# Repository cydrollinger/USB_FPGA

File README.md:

<a href="https://elec-real.com/case-studies/usb-fpga/"></img></a>

> Electronic Realization L.L.C.								  
> Design: Open Hardware Source   USB Configurable Field Programmable Gate Array  	  
>						USB_FPGA board				   
> License: TAPR - http://www.tapr.org/OHL						   
> Engineer: Cy Drollinger								   
> Date: June 26th, 2012								           
> Email: cy@elec-real.com
>Website: https://elec-real.com								   
> Address: 2023 Stadium Dr Suite 2B #210 Bozeman, MT 59715				   
> Phone: 406-539-8117									   

**NOTE:**
 This design has been tested and functions as specified. The design is provided gratis, so, please 
 think critically while utilizing and or redesigning. Open electronic circuitry can be dangerous due 
 to easily shorting circuits which can generate immediate and intense heat resulting in fire. Conversation is
 welcome to improve this design and repository, but, be advised ER is a professional design house and
 monetary compensation is required for additional work toward this design enabling your success.			   

**PURPOSE:**

>**File Arcitecture with a terse description**

* FOLDERS:
	* CDM 2.04.16 WHQL Certified (FTDI.com)
		* WINXP drivers necessary to implement USB configuration of the FPGA (older)
	* CDM 2.04.16 WHQL Certified (FTDI.com)
		* WINXP drivers necessary to implement USB configuration of the FPGA (newer)
	
	* USB_CMD/USB_FPGA: - batch files converting a text document of VHDL into a binary for programming the XC3S250E
		* bin
		* clean
		* clean
		* done_100e.bin
		* done_250e.bin
		* fpga
		* fpga
		* generate
		* generate_100e
		* make
		* make_100e
		* readme
		
	* DOCS/USB_FPGA:
		* may 27 - The goals at the start of the design and the resources utilized 
		* pcb_prob_soulutions - keeping track of flaws and there solutions
		* pds_3an - documentation of the power distribution system designed for the FPGA
		* usb power design - caluculations utilized for the resistor dividers for the LTC3544
	* EAGLE/USB_FPGA:
		* LIBRARY - eagle library files of the electronic parts used in the design
		* eagle.epf - the configuration file of Eaagle Cadsoft for the USB FPGA Open source hardware
		* usb_fpga.sch - Schematic file	
		* usbfpga.brd - board file
		* USB_FPGA.cam - the cam job configuration used to create the gerbers from Eagle 5.10.
	* LICENSE:
		* TAPR_Ope_Hardware_License_v1.0.odt
		* TAPR_Ope_Hardware_License_v1.0.pdf
		* TAPR_Ope_Hardware_License_v1.0.txt
	* MANUFACTURING/USB_FPGA:
		* BOARD ASSEMBLY - files for mounting of the components by automation
		* GERBER - board house files 
		* <a href="https://oshpark.com/shared_projects/XIW354rK"></img></a>
		* PARTS  - order documents for digikey to make a kit for order
	* VHDL/USB_FPGA:
		* FPGA - project files for a 32 bit counter with an upper level 8 bits connected to the LEDS
		* TEST_CPLD - The project files within Xilinx ISE to program the CPLD for slave parallel programming
			    * of the FPGA through the USB via the FT245R.

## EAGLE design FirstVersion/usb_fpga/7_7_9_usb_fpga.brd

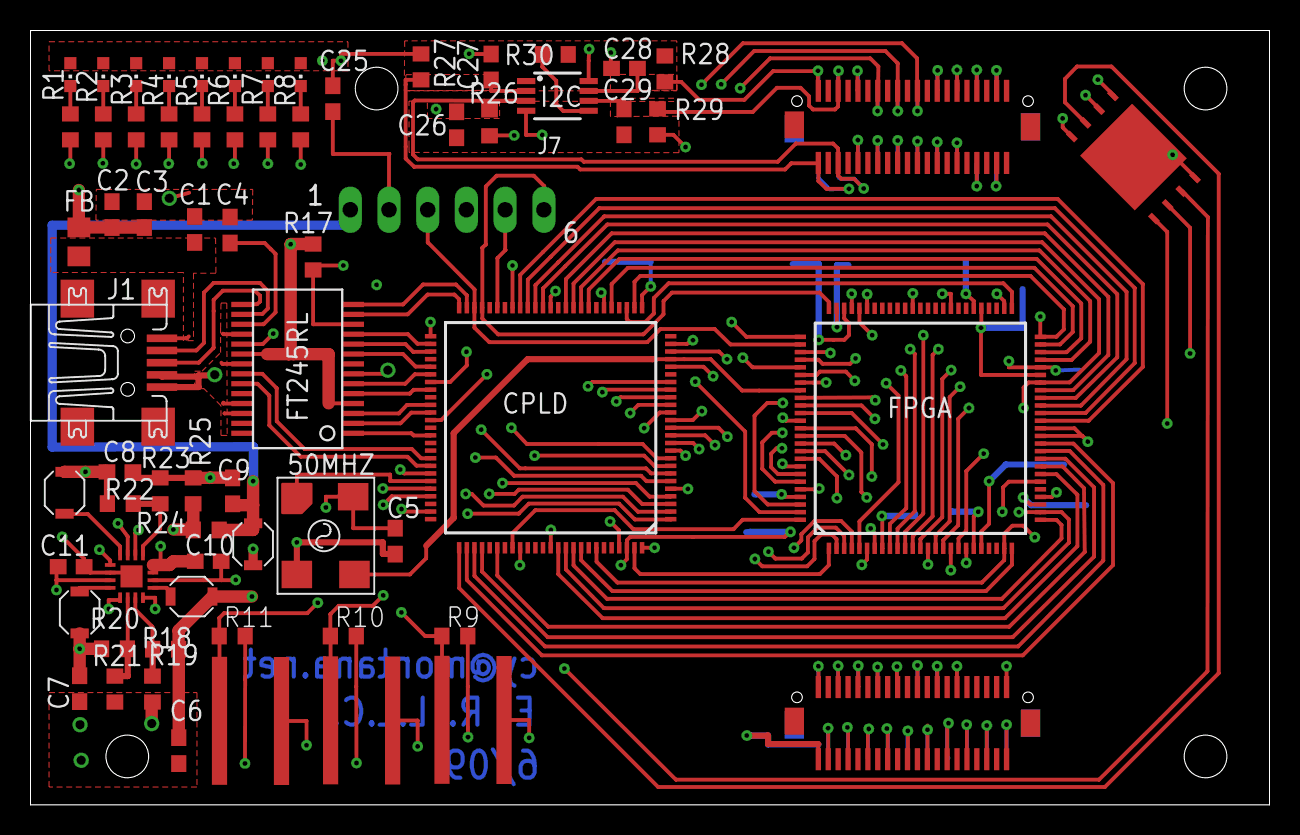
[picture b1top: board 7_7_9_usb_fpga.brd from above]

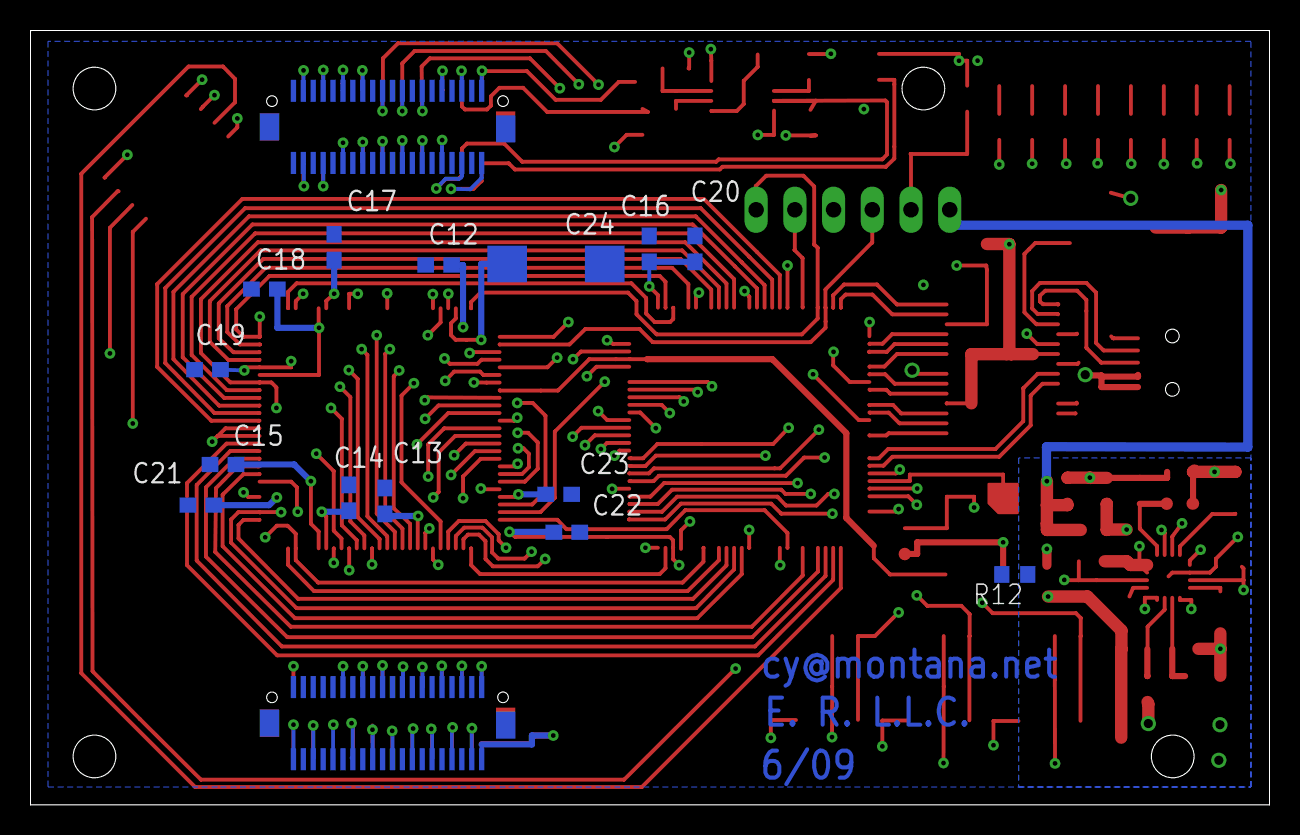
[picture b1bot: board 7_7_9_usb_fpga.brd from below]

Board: 4 copper layers, 81.3 x 50.8 mm, 84 parts (16 on the bottom side), 161 nets.

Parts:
50MHZ: CB3
C1, C5: .01 UF; C0603
C2, C6, C7, C8, C9, C10, C11, C12, C13: 4.7 UF; C0603
C3, C4: .1 UF; C0603
C14, C15, C16, C17: .47 UF; C0603
C18, C19, C20, C21, C22, C23: .047 UF; C0603
C24: 470 UF; CT7343
C25, C26, C27, C28, C29: 50 PF; C0603
CPLD: XC2C64A_VQ100; VQ100
FB: 1uH; R0805
FPGA: XC3S100E_VQ100; VQ100
FT245RL: FT245RL; SSOP28DB
I2C: LTC4300-1; MSOP8
J1: MINI-USB; UX60-MB-5ST
J3, J5: DF15_40; DF15
J4, J6: DF15_40_; DF15_
J7: 22-27-2061-06; 6410-06
L1, L2, L3, L4: 4.7 UH; L3010
LED1, LED2, LED3, LED4, LED5, LED6, LED7, LED8: CHIPLED_0603
R1, R2, R3, R4, R5, R6, R7, R8: R0603
R9, R10, R11, R17: 10k; R0603
R12: 0; R0603
R18: 500; R0603
R19, R21, R23, R25: 1k3; R0603
R20: 3125; R0603
R22: 1250; R0603
R24: 2125; R0603
R26, R27, R28, R29: 20 k; R0603
R30: 10 k; R0603
SPI_FLASH: M25P16; VDFPN8
SW1, SW2, SW3: BS3N
VOLTAGE_REG: LTC3544; QFN16

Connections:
1.8V: C8.1, C16.1, C20.1, CPLD.26, CPLD.57, L3.P$1, R22.2
AGND: C6.2, C7.2, C8.2, C9.2, C10.2, C11.1, R12.1, R19.1, R21.1, R23.1, R25.1, VOLTAGE_REG.6, VOLTAGE_REG.14, VOLTAGE_REG.P$17
BUSY: CPLD.91, FPGA.26
CCLK: CPLD.27, FPGA.50, SPI_FLASH.6
CE: 50MHZ.1, CPLD.70
CSO_B: CPLD.94, FPGA.24, SPI_FLASH.1
D0: CPLD.64, FT245RL.1
D1: CPLD.58, FT245RL.5
D2: CPLD.60, FT245RL.3
D3: CPLD.52, FT245RL.11
D4: CPLD.61, FT245RL.2
D5: CPLD.55, FT245RL.9
D6: CPLD.53, FT245RL.10
D7: CPLD.56, FT245RL.6
DGND: 50MHZ.2, C1.2, C2.2, C3.2, C4.2, C5.1, C12.2, C13.2, C14.2, C15.2, C16.2, C17.2, C18.2, C19.2, C20.2, C21.2, C22.2, C23.2, C24.-, C25.2, C26.2, C27.2, C28.2, C29.2, CPLD.21, CPLD.31, CPLD.62, CPLD.69, CPLD.84, CPLD.100, FPGA.7, FPGA.14, FPGA.19, FPGA.29, FPGA.37, FPGA.38, FPGA.52, FPGA.59, FPGA.64, FPGA.72, FPGA.81, FPGA.87, FPGA.93, FT245RL.7, FT245RL.18, FT245RL.21, FT245RL.25, FT245RL.26, I2C.4, J1.4, J1.5, J3.P$21, J4.P$20, J7.2, R12.2, SPI_FLASH.4, SW1.2, SW2.2, SW3.2
DIN/_D0: CPLD.35, FPGA.44, SPI_FLASH.2
DONE: CPLD.28, FPGA.51
FPGA_TDI: CPLD.83, FPGA.100
HOLD: CPLD.76, SPI_FLASH.7
HSWAP: CPLD.24, FPGA.99
INIT_B: CPLD.92, FPGA.25
J3_2: CPLD.10, J3.P$2, J4.P$39
J3_3: J3.P$3, J4.P$38
J3_4: CPLD.11, J3.P$4, J4.P$37
J3_5: J3.P$5, J4.P$36
J3_6: CPLD.12, J3.P$6, J4.P$35
J3_7: J3.P$7, J4.P$34
J3_8: CPLD.13, J3.P$8, J4.P$33
J3_9: J3.P$9, J4.P$32
J3_10: CPLD.23, J3.P$10, J4.P$31
J3_11: J3.P$11, J4.P$30
J3_12: CPLD.15, J3.P$12, J4.P$29
J3_13: J3.P$13, J4.P$28
J3_14: CPLD.16, J3.P$14, J4.P$27
J3_15: J3.P$15, J4.P$26
J3_16: CPLD.17, J3.P$16, J4.P$25
J3_17: J3.P$17, J4.P$24
J3_18: CPLD.18, J3.P$18, J4.P$23
J3_19: J3.P$19, J4.P$22
J3_20: CPLD.19, J3.P$20, J4.P$21
J3_22: J3.P$22, J4.P$19
J3_23: J3.P$23, J4.P$18
J3_24: J3.P$24, J4.P$17
J3_25: J3.P$25, J4.P$16
J3_26: FPGA.84, J3.P$26, J4.P$15
J3_27: J3.P$27, J4.P$14
J3_28: FPGA.85, J3.P$28, J4.P$13
J3_29: J3.P$29, J4.P$12
J3_30: FPGA.86, J3.P$30, J4.P$11
J3_31: J3.P$31, J4.P$10
J3_32: FPGA.88, J3.P$32, J4.P$9
J3_33: J3.P$33, J4.P$8
J3_34: FPGA.89, J3.P$34, J4.P$7
J3_35: J3.P$35, J4.P$6
J3_36: FPGA.90, J3.P$36, J4.P$5
J3_37: J3.P$37, J4.P$4
J3_38: FPGA.91, J3.P$38, J4.P$3
J3_39: J3.P$39, J4.P$2
J3_40: FPGA.92, J3.P$40, J4.P$1
J5_1: C27.1, FPGA.5, I2C.2, J5.P$1, J6.P$40, R27.1
J5_2: J5.P$2, J6.P$39
J5_3: C26.1, FPGA.9, I2C.3, J5.P$3, J6.P$38, R26.1
J5_4: J5.P$4, J6.P$37
J5_5: FPGA.10, J5.P$5, J6.P$36
J5_6: J5.P$6, J6.P$35
J5_7: FPGA.11, J5.P$7, J6.P$34
J5_8: J5.P$8, J6.P$33
J5_9: FPGA.12, J5.P$9, J6.P$32
J5_10: J5.P$10, J6.P$31
J5_11: FPGA.13, J5.P$11, J6.P$30
J5_12: J5.P$12, J6.P$29
J5_13: FPGA.15, J5.P$13, J6.P$28
J5_14: J5.P$14, J6.P$27
J5_15: FPGA.16, J5.P$15, J6.P$26
J5_16: J5.P$16, J6.P$25
J5_17: FPGA.17, J5.P$17, J6.P$24
J5_18: J5.P$18, J6.P$23
J5_19: FPGA.18, J5.P$19, J6.P$22
J5_20: J5.P$20, J6.P$21
J5_21: J5.P$21, J6.P$20
J5_22: FPGA.70, J5.P$22, J6.P$19
J5_23: J5.P$23, J6.P$18
J5_24: FPGA.71, J5.P$24, J6.P$17
J5_25: J5.P$25, J6.P$16
J5_26: FPGA.79, J5.P$26, J6.P$15
J5_27: J5.P$27, J6.P$14
J5_28: FPGA.78, J5.P$28, J6.P$13
J5_29: J5.P$29, J6.P$12
J5_30: FPGA.98, J5.P$30, J6.P$11
J5_31: J5.P$31, J6.P$10
J5_32: FPGA.95, J5.P$32, J6.P$9
J5_33: J5.P$33, J6.P$8
J5_34: FPGA.94, J5.P$34, J6.P$7
J5_35: J5.P$35, J6.P$6
J5_36: FPGA.2, J5.P$36, J6.P$5
J5_37: J5.P$37, J6.P$4
J5_38: C29.1, FPGA.3, I2C.6, J5.P$38, J6.P$3, R29.1
J5_39: J5.P$39, J6.P$2
J5_40: C28.1, FPGA.4, I2C.7, J5.P$40, J6.P$1, R28.1
LED1: CPLD.1, R1.1
LED2: CPLD.2, R2.1
LED3: CPLD.3, R3.1
LED4: CPLD.4, R4.1
LED5: CPLD.6, R5.1
LED6: CPLD.7, R6.1
LED7: CPLD.8, R7.1
LED8: CPLD.9, R8.1
M0: CPLD.36, FPGA.43
M1: CPLD.39, FPGA.42
M2: CPLD.42, FPGA.39
MCLK: 50MHZ.3, CPLD.22, FPGA.83
MOSI: CPLD.90, FPGA.27, SPI_FLASH.5
unnamed: R22.1, R23.2, VOLTAGE_REG.1
unnamed: R24.1, R25.2, VOLTAGE_REG.2
unnamed: R18.1, R19.2, VOLTAGE_REG.11
unnamed: C1.1, FB.1, J1.1
unnamed: R20.1, R21.2, VOLTAGE_REG.10
unnamed: L1.P$1, VOLTAGE_REG.13
unnamed: L4.P$1, VOLTAGE_REG.8
unnamed: L2.P$2, VOLTAGE_REG.5
unnamed: L3.P$2, VOLTAGE_REG.4
unnamed: I2C.5, R30.1
unnamed: C4.1, FT245RL.17
unnamed: LED1.C, R1.2
unnamed: LED2.C, R2.2
unnamed: LED3.C, R3.2
unnamed: LED4.C, R4.2
unnamed: LED5.C, R5.2
unnamed: LED6.C, R6.2
unnamed: LED7.C, R7.2
unnamed: LED8.C, R8.2
PROG_B: CPLD.99, FPGA.1
PWREN: CPLD.43, FT245RL.12, R17.1
RD: CPLD.50, FT245RL.13
RST: CPLD.14, FT245RL.19
RX: CPLD.68, FT245RL.23
SW1: CPLD.74, R9.1, SW1.1
SW2: CPLD.72, R10.1, SW2.1
SW3: CPLD.71, R11.1, SW3.1
TCK: CPLD.48, FPGA.77, J7.3
TDI: CPLD.45, J7.5
TDO: FPGA.76, J7.4
TMS: CPLD.47, FPGA.75, J7.6
TX: CPLD.67, FT245RL.22
USBDM: FT245RL.16, J1.2
USBDP: FT245RL.15, J1.3
VCC: C2.1, C3.1, C10.1, C11.2, FB.2, J3.P$1, J4.P$40, VOLTAGE_REG.3, VOLTAGE_REG.7, VOLTAGE_REG.9, VOLTAGE_REG.12, VOLTAGE_REG.15, VOLTAGE_REG.16
VCCAUX: C9.1, C12.1, C15.1, C19.1, CPLD.5, FPGA.21, FPGA.46, FPGA.74, FPGA.96, J7.1, L2.P$1, R24.2
VCCINT: C6.1, C17.1, C21.1, FPGA.6, FPGA.28, FPGA.56, FPGA.80, L1.P$2, R18.2
VCCO: 50MHZ.4, C5.2, C7.1, C13.1, C14.1, C18.1, C22.1, C23.1, C24.+, C25.1, CPLD.38, CPLD.51, CPLD.88, CPLD.98, FPGA.8, FPGA.20, FPGA.31, FPGA.45, FPGA.55, FPGA.73, FPGA.82, FPGA.97, FT245RL.4, FT245RL.20, I2C.8, L4.P$2, LED1.A, LED2.A, LED3.A, LED4.A, LED5.A, LED6.A, LED7.A, LED8.A, R9.2, R10.2, R11.2, R17.2, R20.2, R26.2, R27.2, R28.2, R29.2, R30.2, SPI_FLASH.8
VS0: CPLD.30, FPGA.49
VS1: CPLD.33, FPGA.48
VS2: CPLD.34, FPGA.47
WR: CPLD.49, FT245RL.14
_D1: CPLD.40, FPGA.41
_D2: CPLD.41, FPGA.40
_D3: CPLD.77, FPGA.36
_D4: CPLD.78, FPGA.35
_D5: CPLD.79, FPGA.34
_D6: CPLD.81, FPGA.33
_D7: CPLD.89, FPGA.32

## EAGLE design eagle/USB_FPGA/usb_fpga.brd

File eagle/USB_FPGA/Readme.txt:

********************************************************************************************
* Electronic Realization L.L.C.								   *
* Design: Open Hardware Source   USB Configurable Field Programmable Gate Array  	   *
*						USB_FPGA board				   *
* License: TAPR - http://www.tapr.org/OHL						   *
* Engineer: Cy Drollinger								   *
* Date: June 26th, 2012								           *
* Email: cy@elec-real.com								   *
* Address: 313 W. mendenhall #5 Bozeman, MT 59715					   *
* Phone: 406-586-5502									   *
********************************************************************************************

*******************************************
*File Arcitecture with a small description*
*******************************************
FOLDERS/files:
	EAGLE/USB_FPGA:
		LIBRARY - eagle library files of the electronic parts used in the design
		eagle.epf - the configuration file of Eaagle Cadsoft for the USB FPGA Open source hardware
		usb_fpga.sch - Schematic file	
		usbfpga.brd - board file
		USB_FPGA.cam - the cam job configuration used to create the gerbers from Eagle 5.10.

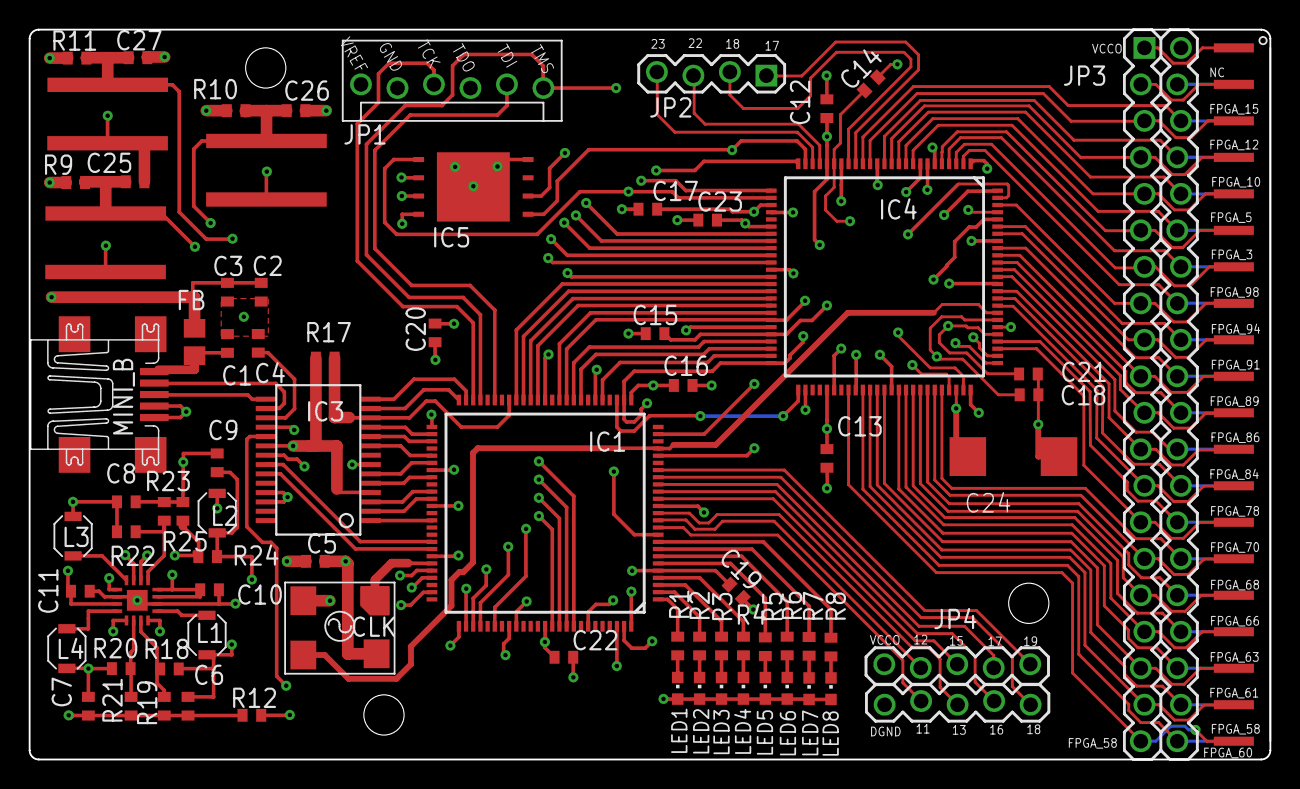
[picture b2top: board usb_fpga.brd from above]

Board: 4 copper layers, 86.4 x 50.8 mm, 77 parts (0 on the bottom side), 133 nets.

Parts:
C1, C5: .01 UF; C0402
C2, C6, C7, C8, C9, C10, C11, C12, C13: 4.7 UF; C0402
C3, C4: .1 UF; C0402
C14, C15, C16, C17: .47 UF; C0402
C18, C19, C20, C21, C22, C23: .047 UF; C0402
C24: 470 uF; D/7343-31R
C25, C26, C27: C0402
CLK: 50MHz; CB3
FB: 1uH; R0805
IC1: XC2C64A_VQ100; VQ100
IC2: LTC3544; QFN16
IC3: FT245RL; SSOP28DB
IC4: XC3S250E_VQ100; VQ100
IC5: M25P16; VDFPN8
JP1: MOLEX-1X6_LOCK
JP2: 1X04_LOCK
JP3: LOCK_40
JP4, JP4_1: 1X05_LOCK
JP36: BRD_EDGE_40; STRADDLE_40
L1, L2, L3, L4: 4.7 uH; L3010
LED1, LED2, LED3, LED4, LED5, LED6, LED7, LED8: CHIPLED_0603
MINI_B: none; UX60A-MB-5ST
R1, R2, R3, R4, R5, R6, R7, R8: R0402
R9, R10, R11, R17: 10k; R0402
R12: 0; R0402
R18: 500; R0402
R19, R21, R23, R25: 1k3; R0402
R20: 3125; R0402
R22: 1250; R0402
R24: 2125; R0402
SW1, SW2, SW3: BS3N

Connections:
1.8V: C8.1, C16.1, C20.1, IC1.26, IC1.57, L3.P$1, R22.2
AGND: C6.2, C7.2, C8.2, C9.2, C10.2, C11.1, IC2.6, IC2.14, IC2.P$17, R12.1, R19.1, R21.1, R23.1, R25.1
BUSY: IC1.91, IC4.26
CCLK: IC1.27, IC4.50, IC5.6
CE: CLK.1, IC1.70
CPLD_11: IC1.11, JP4_1.4
CPLD_12: IC1.12, JP4.2
CPLD_13: IC1.13, JP4_1.3
CPLD_15: IC1.15, JP4.3
CPLD_16: IC1.16, JP4_1.2
CPLD_17: IC1.17, JP4.4
CPLD_18: IC1.18, JP4_1.1
CPLD_19: IC1.19, JP4.5
CSO_B: IC1.94, IC4.24, IC5.1
D0: IC1.64, IC3.1
D1: IC1.58, IC3.5
D2: IC1.60, IC3.3
D3: IC1.52, IC3.11
D4: IC1.61, IC3.2
D5: IC1.55, IC3.9
D6: IC1.53, IC3.10
D7: IC1.56, IC3.6
DGND: C1.2, C2.2, C3.2, C4.2, C5.1, C12.2, C13.2, C14.2, C15.2, C16.2, C17.2, C18.2, C19.2, C20.2, C21.2, C22.2, C23.2, C24.-, C25.2, C26.2, C27.2, CLK.2, IC1.21, IC1.31, IC1.62, IC1.69, IC1.84, IC1.100, IC3.7, IC3.18, IC3.21, IC3.25, IC3.26, IC4.7, IC4.14, IC4.19, IC4.29, IC4.37, IC4.52, IC4.59, IC4.64, IC4.72, IC4.81, IC4.87, IC4.93, IC5.4, JP1.2, JP3.40, JP4_1.5, JP36.P$40, MINI_B.4, MINI_B.5, R12.2, SW1.2, SW2.2, SW3.2
DIN/_D0: IC1.35, IC4.44, IC5.2
DONE: IC1.28, IC4.51
FPGA_2: IC4.2, JP3.33, JP36.P$33
FPGA_3: IC4.3, JP3.7, JP36.P$7
FPGA_4: IC4.4, JP3.34, JP36.P$34
FPGA_5: IC4.5, JP3.6, JP36.P$6
FPGA_9: IC4.9, JP3.35, JP36.P$35
FPGA_10: IC4.10, JP3.5, JP36.P$5
FPGA_11: IC4.11, JP3.36, JP36.P$36
FPGA_12: IC4.12, JP3.4, JP36.P$4
FPGA_13: IC4.13, JP3.37, JP36.P$37
FPGA_15: IC4.15, JP3.3, JP36.P$3
FPGA_16: IC4.16, JP3.38, JP36.P$38
FPGA_17: IC4.17, JP2.1
FPGA_18: IC4.18, JP2.2
FPGA_22: IC4.22, JP2.3
FPGA_23: IC4.23, JP2.4
FPGA_58: IC4.58, JP3.20, JP36.P$20
FPGA_60: IC4.60, JP3.21, JP36.P$21
FPGA_61: IC4.61, JP3.19, JP36.P$19
FPGA_62: IC4.62, JP3.22, JP36.P$22
FPGA_63: IC4.63, JP3.18, JP36.P$18
FPGA_65: IC4.65, JP3.23, JP36.P$23
FPGA_66: IC4.66, JP3.17, JP36.P$17
FPGA_67: IC4.67, JP3.24, JP36.P$24
FPGA_68: IC4.68, JP3.16, JP36.P$16
FPGA_69: IC4.69, JP3.25, JP36.P$25
FPGA_70: IC4.70, JP3.15, JP36.P$15
FPGA_71: IC4.71, JP3.26, JP36.P$26
FPGA_78: IC4.78, JP3.14, JP36.P$14
FPGA_79: IC4.79, JP3.27, JP36.P$27
FPGA_84: IC4.84, JP3.13, JP36.P$13
FPGA_85: IC4.85, JP3.28, JP36.P$28
FPGA_86: IC4.86, JP3.12, JP36.P$12
FPGA_88: IC4.88, JP3.29, JP36.P$29
FPGA_89: IC4.89, JP3.11, JP36.P$11
FPGA_90: IC4.90, JP3.30, JP36.P$30
FPGA_91: IC4.91, JP3.10, JP36.P$10
FPGA_92: IC4.92, JP3.31, JP36.P$31
FPGA_94: IC4.94, JP3.9, JP36.P$9
FPGA_95: IC4.95, JP3.32, JP36.P$32
FPGA_98: IC4.98, JP3.8, JP36.P$8
FPGA_TDI: IC1.83, IC4.100
HOLD: IC1.76, IC5.7
HSWAP: IC1.24, IC4.99
INIT_B: IC1.92, IC4.25
L2: JP3.2, JP36.P$2
L39: JP3.39, JP36.P$39
LED1: IC1.1, R1.1
LED2: IC1.2, R2.1
LED3: IC1.3, R3.1
LED4: IC1.4, R4.1
LED5: IC1.6, R5.1
LED6: IC1.7, R6.1
LED7: IC1.8, R7.1
LED8: IC1.9, R8.1
M0: IC1.36, IC4.43
M1: IC1.39, IC4.42
M2: IC1.42, IC4.39
MCLK: CLK.3, IC1.22, IC4.83
MOSI: IC1.90, IC4.27, IC5.5
unnamed: IC2.1, R22.1, R23.2
unnamed: IC2.2, R24.1, R25.2
unnamed: IC2.11, R18.1, R19.2
unnamed: C1.1, FB.1, MINI_B.1
unnamed: IC2.10, R20.1, R21.2
unnamed: IC2.13, L1.P$1
unnamed: IC2.8, L4.P$1
unnamed: IC2.5, L2.P$2
unnamed: IC2.4, L3.P$2
unnamed: C4.1, IC3.17
unnamed: LED1.C, R1.2
unnamed: LED2.C, R2.2
unnamed: LED3.C, R3.2
unnamed: LED4.C, R4.2
unnamed: LED5.C, R5.2
unnamed: LED6.C, R6.2
unnamed: LED7.C, R7.2
unnamed: LED8.C, R8.2
PROG_B: IC1.99, IC4.1
PWREN: IC1.43, IC3.12, R17.1
RD: IC1.50, IC3.13
RDWR_B: IC1.10, IC4.38
RST: IC1.14, IC3.19
RX: IC1.68, IC3.23
SW1: C25.1, IC1.74, R9.1, SW1.1
SW2: C26.1, IC1.72, R10.1, SW2.1
SW3: C27.1, IC1.71, R11.1, SW3.1
TCK: IC1.48, IC4.77, JP1.3
TDI: IC1.45, JP1.5
TDO: IC4.76, JP1.4
TMS: IC1.47, IC4.75, JP1.6
TX: IC1.67, IC3.22
USBDM: IC3.16, MINI_B.2
USBDP: IC3.15, MINI_B.3
VCC: C2.1, C3.1, C10.1, C11.2, FB.2, IC2.3, IC2.7, IC2.9, IC2.12, IC2.15, IC2.16
VCCAUX: C9.1, C12.1, C15.1, C19.1, IC1.5, IC4.21, IC4.46, IC4.74, IC4.96, JP1.1, L2.P$1, R24.2
VCCINT: C6.1, C17.1, C21.1, IC4.6, IC4.28, IC4.56, IC4.80, L1.P$2, R18.2
VCCO: C5.2, C7.1, C13.1, C14.1, C18.1, C22.1, C23.1, C24.+, CLK.4, IC1.38, IC1.51, IC1.88, IC1.98, IC3.4, IC3.20, IC4.8, IC4.20, IC4.31, IC4.45, IC4.55, IC4.73, IC4.82, IC4.97, IC5.8, JP3.1, JP4.1, JP36.P$1, L4.P$2, LED1.A, LED2.A, LED3.A, LED4.A, LED5.A, LED6.A, LED7.A, LED8.A, R9.2, R10.2, R11.2, R17.2, R20.2
VS0: IC1.30, IC4.49
VS1: IC1.33, IC4.48
VS2: IC1.34, IC4.47
WR: IC1.49, IC3.14
_D1: IC1.40, IC4.41
_D2: IC1.41, IC4.40
_D3: IC1.77, IC4.36
_D4: IC1.78, IC4.35
_D5: IC1.79, IC4.34
_D6: IC1.81, IC4.33
_D7: IC1.89, IC4.32

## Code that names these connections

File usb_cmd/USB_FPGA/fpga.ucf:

NET "mclk" LOC = "P83";
#NET "PROG_B" LOC = "P1";
#NET "J5_36" LOC = "P2";
#NET "J5_38" LOC = "P3";
#NET "J5_40" LOC = "P4";
#NET "J5_1" LOC = "P5";
#NET "J5_3" LOC = "P7";
#NET "J5_5" LOC = "10";
#NET "J5_7" LOC = "P11";
#NET "J5_9" LOC = "P12";
#NET "J5_11" LOC = "P13";
#NET "J5_13" LOC = "P15";
#NET "J5_15" LOC = "P16";
#NET "J5_17" LOC = "P17";
#NET "J5_19" LOC = "P18";
#NET "CSO_B" LOC = "P24";
#NET "INIT_B" LOC = "P25";
#NET "BUSY" LOC = "P26";
#NET "MOSI" LOC = "P27";
NET "D<7>" LOC = "P32";
NET "D<6>" LOC = "P33";
NET "D<5>" LOC = "P34";
NET "D<4>" LOC = "P35";
NET "D<3>" LOC = "P36";
#NET "M<2>" LOC = "P39";
NET "D<2>" LOC = "P40";
NET "D<1>" LOC = "P41";
#NET "M<1>" LOC = "P42";
#NET "M<0>" LOC = "P43";
NET "D<0>" LOC = "P44";
#NET "VS2" LOC = "P47";
#NET "VS1" LOC = "P48";
#NET "VS0" LOC = "P49";
#NET "cclk" LOC = "P50";
#NET "J5_22" LOC = "P70";
#NET "J5_24" LOC = "P71";
#NET "J5_26" LOC = "P78";
#NET "J5_28" LOC = "P79";
#NET "J3_26" LOC = "P84";
#NET "J3_28" LOC = "P85";
#NET "J3_30" LOC = "P86";
#NET "J3_32" LOC = "P88";
#NET "J3_34" LOC = "P89";
#NET "J3_36" LOC = "P90";
#NET "J3_38" LOC = "P91";
#NET "J3_40" LOC = "P92";
#NET "J5_34" LOC = "P94";
#NET "J5_32" LOC = "P95";
#NET "J5_30" LOC = "P98";
#NET "HSWAP" LOC = "P99";

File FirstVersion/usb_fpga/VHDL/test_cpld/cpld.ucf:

NET "mclk" LOC = "P22";
NET "mclk_ce" LOC = "P70";
#NET "VARIANT(0)" LOC = "P30";
#NET "VARIANT(1)" LOC = "P33";
#NET "VARIANT(2)" LOC = "P34";
NET "MODE(0)" LOC = "P36";
NET "MODE(1)" LOC = "P39";
NET "MODE(2)" LOC = "P42";
NET "FPGA_MOSI" LOC = ""P90;
#NET "FPGA_BUSY" LOC = "P91";
NET "FPGA_INITB" LOC = "P92";
#NET "FPGA_CSO_B" LOC = "P94";
NET "FPGA_done" LOC = "P28";
NET "FPGA_prog_b" LOC = "P99";
NET "FPGA_cclk" LOC = "P27";
#NET "FPGA_HSWAP" LOC = "P24";
#NET "SPI_flash_HOLD" LOC = "P76";
#NET "SPI_flash_W" LOC = "97";
NET "FPGA_D(0)" LOC = "P35" ;
NET "FPGA_D(1)" LOC = "P40" ;
NET "FPGA_D(2)" LOC = "P41" ;
NET "FPGA_D(3)" LOC = "P77" ;
NET "FPGA_D(4)" LOC = "P78" ;
NET "FPGA_D(5)" LOC = "P79" ;
NET "FPGA_D(6)" LOC = "P81" ;
NET "FPGA_D(7)" LOC = "P89" ;

NET "SW(0)" LOC = "71" | PULLUP;
NET "SW(1)" LOC = "72" | PULLUP;
NET "SW(2)" LOC = "74" | PULLUP;

NET N24		LOC = "29";

NET "LEDs(1)" LOC = "P1" ;
NET "LEDs(2)" LOC = "P2" ;
NET "LEDs(3)" LOC = "P3" ;
NET "LEDs(4)" LOC = "P4" ;
NET "LEDs(5)" LOC = "P6" ;
NET "LEDs(6)" LOC = "P7" ;
NET "LEDs(7)" LOC = "P8" ;
NET "LEDs(8)" LOC = "P9" ;

#NET "J3_2" LOC = "P10";
#NET "J3_4" LOC = "P11";
#NET "J3_6" LOC = "P12";
#NET "J3_8" LOC = "P13";
#NET "J3_12" LOC = "P15";
#NET "J3_14" LOC = "P16";
#NET "J3_16" LOC = "P17";
#NET "J3_18" LOC = "P18";
#NET "J3_20" LOC = "P19";
#
#NET "usb_pwren" LOC = "P43";
#NET "usb_wr" LOC = "P49";
NET "usb_rd" LOC = "P50";
NET "data(0)" LOC = "P64";
NET "data(1)" LOC = "P58";
NET "data(2)" LOC = "P60";
NET "data(3)" LOC = "P52";
NET "data(4)" LOC = "P61";
NET "data(5)" LOC = "P55";
NET "data(6)" LOC = "P53";
NET "data(7)" LOC = "P56";
#NET "usb_tx" LOC = "P67";
NET "usb_rx" LOC = "P68";
NET "usb_rst" LOC ="P14";

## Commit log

2019-04-05 first commit 4/5/19
2019-04-06 changed the url for board 4/6/19
2019-04-06 changed address and ph # 4/6/19
2019-04-18 First commit for elec-real.com 4/19
2019-04-18 first commit of files 4/18/19
2019-04-26 first commit 4/26/19
2019-04-27 first commit 4/27/19
2019-04-30 first commit 4/30/19
